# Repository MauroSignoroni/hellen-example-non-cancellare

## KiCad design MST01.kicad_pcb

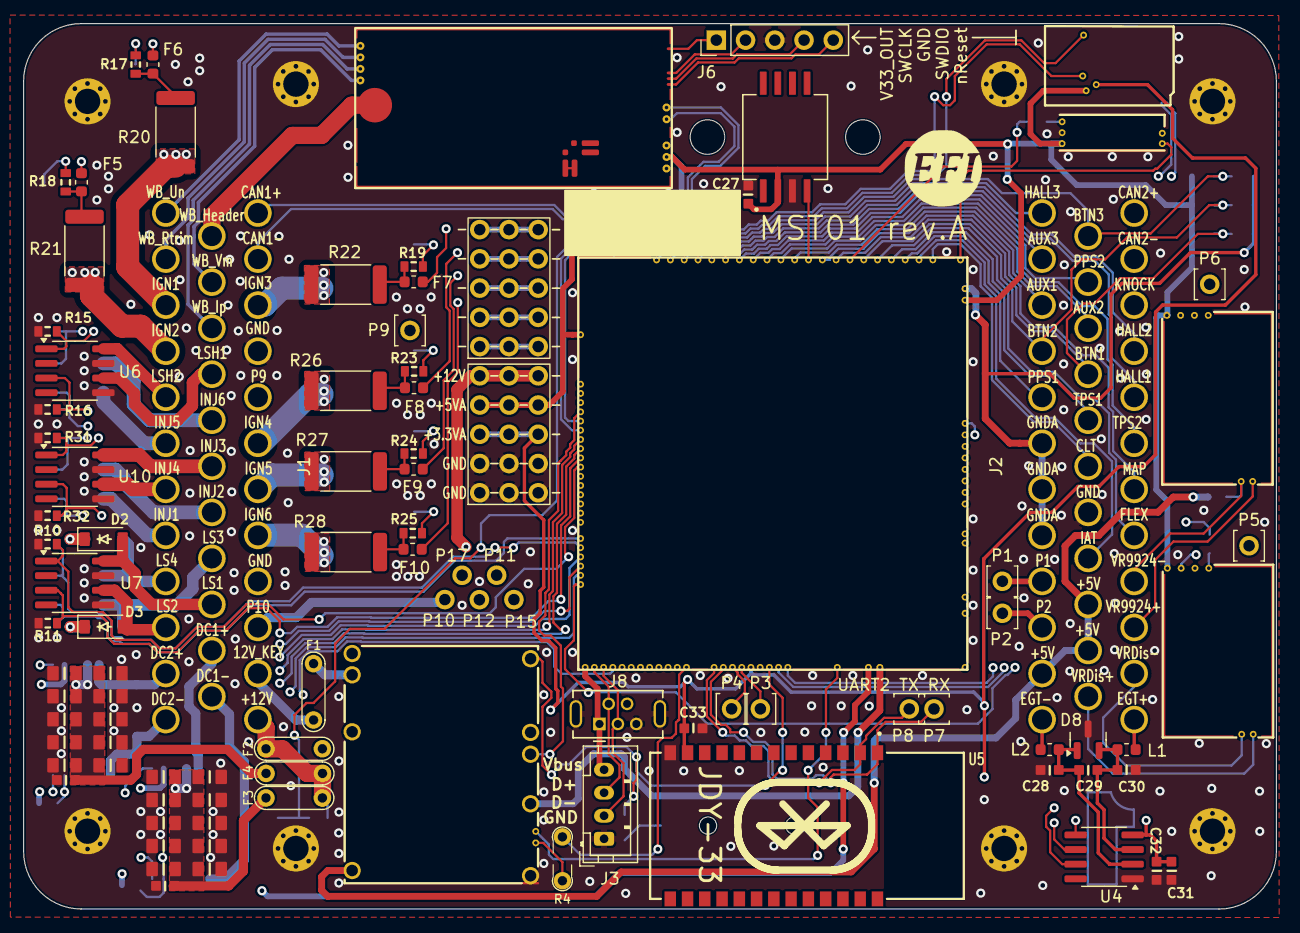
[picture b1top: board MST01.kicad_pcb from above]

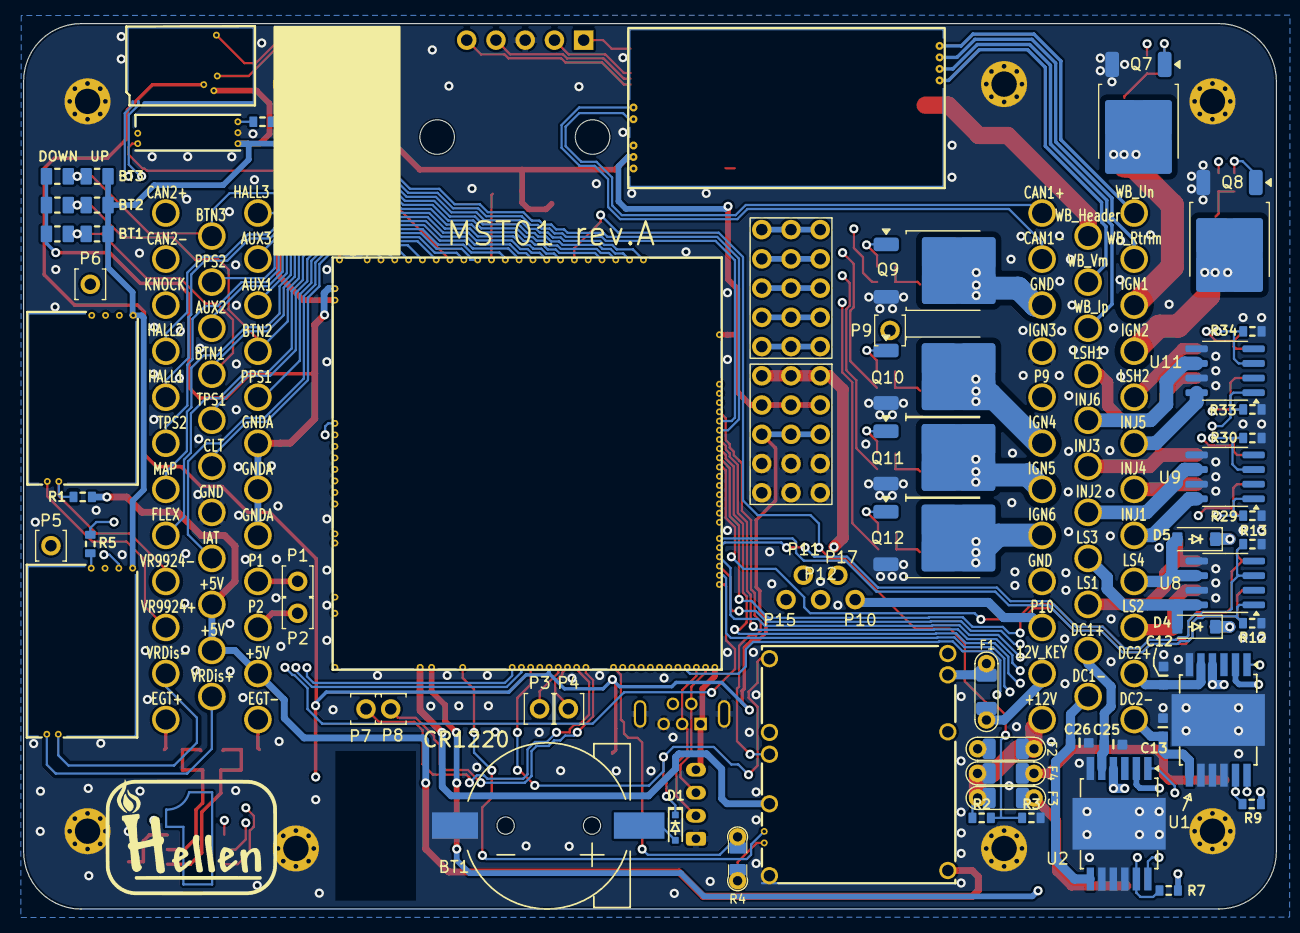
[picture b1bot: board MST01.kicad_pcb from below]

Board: 4 copper layers, 108.8 x 76.9 mm, 139 parts (45 on the bottom side), 147 nets.

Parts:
BT1: CR1220; CR1220-2
C1, C2, C3, C4, C5, C6, C7, C8, C9, C10, C14, C15, C16, C17, C18, C19, C20, C21, C22, C23: 10u; C0805
C11, C24, C27, C29, C31, C33: 100n; C0603
C12, C13, C25, C26, C28, C30: 10n; C0603
C32: 1u; C0603
D1: 1N4148WS; SOD-323
D2, D3, D4, D5: B5819W; SOD-123
D8: NUP2105L; SOT-23
F1, F2, F3, F4: 12H1500D; PAD-1206-PAD
F5, F6, F7, F8, F9, F10: 50mA; Fuse_0603_1608Metric
G1: RUSEFI_LOGO; rusefi_logo
G2: LOGO
G3, G4: PROTO_AREA
H1, H2: MountingHole; MountingHole_3mm
J1: AMPSeal-35-verticale-nero; ampseal-35-mia-con-pad-GND
J2: AMPSeal-35-verticale-bianco; ampseal-35-mia-con-pad-GND
J3: Conn_01x04_Pin; JST_PH_B4B-PH-K_1x04_P2.00mm_Vertical
J6: Conn_01x05_Pin; PinHeader_1x05_P2.54mm_Vertical
J8: USB_B_Mini; USB-MINI-B-VERTICAL
L1, L2: 470R@100MHz; L_0603_1608Metric
M1: Module-power_12and5V-0.3; power_12and5V
M2: Module-knock-0.2; knock
M3: Module-vr-discrete-0.5; vr-discrete
M4: Module-vr-max9924-0.1; vr-max9924
M5: Module-wbo-0.5; wbo
M6: Module:mega-mcu100/0.3; mega-mcu100
M7: Module-can-0.1; can
P1, P2, P3, P4, P5, P6, P7, P8, P9: Pad; PAD-TH
P10, P11, P12, P15, P17: Pad; PAD-TH-senza-serigrafia
Q7, Q8, Q9, Q10, Q11, Q12: ISL9V3040D3ST; TO-252-2
R1, R7, R9, R10, R11, R12, R13, R15, R16, R29, R30, R31, R32, R33, R34: 4.7k; R0603
R2: 33k; R0603
R3: 6.8k; R0603
R4: Jumper-Pad-Pad; PAD-0805-PAD
R5, R6: 0; R0603
R17, R18, R19, R23, R24, R25: 22; R0603
R20, R21, R22, R26, R27, R28: 0; R_2512_6332Metric
R35, R36, R37, R38, R39, R40: 10k; R0805
U1, U2: TLE9201SG; Infineon_PG-DSO-12-11
U4: MAX31855KASA; SOIC-8_3.9x4.9mm_P1.27mm
U5: JDY-33; JDY-33_mio
U6, U7, U8, U9, U10, U11: VNLD5160TR-E; SOIC-8_3.9x4.9mm_P1.27mm
U12: MPXH6400A; MPXH6400A-SSOP8

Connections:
+3.3V: M6.N21 (V33), R7.2, R9.2, U1.2 (VSO), U2.2 (VSO)
+3.3VA: C31.2, C32.2, C33.2, G3.3, G3.8, G3.13, M6.N15 (V33_SWITCHABLE), M7.V2 (CAN_VIO), U4.4 (V_{CC}), U5.12 (3V3)
+5V: M1.E4 (V5), M6.N22 (VCC)
+5VA: C27.2, G3.4, G3.9, G3.14, M2.E1 (V5A), M3.E4 (V5_IN), M4.E4 (V5_IN), M5.W1 (V5_IN), M6.E1 (V5A_SWITCHABLE), M6.W2 (V5A_SWITCHABLE), M7.V1 (V5), R38.2, R39.2, R40.2, U12.2 (Vs)
+5VP: J2.21, J2.22, J2.34, M1.V4 (5VP), R1.1
+12V: F2.1, F3.1, F4.1, J1.24, R2.2
+12V_RAW: D2.1 (K), D3.1 (K), D4.1 (K), D5.1 (K), F2.2, G3.5, G3.10, G3.15, M1.V1 (V12_PERM), M1.V3 (V12_RAW)
/2 DC Driver/PWR1: C1.2, C2.2, C3.2, C4.2, C5.2, C6.2, C7.2, C8.2, C9.2, C10.2, C11.2, F4.2, U1.4 (VS)
/2 DC Driver/PWR2: C14.2, C15.2, C16.2, C17.2, C18.2, C19.2, C20.2, C21.2, C22.2, C23.2, C24.2, F3.2, U2.4 (VS)
/12V_KEY: F1.1, J1.25
/ADC3: M6.S15 (IN_KNOCK_(PA2)), R5.2, R6.2
/AUX1: J2.26, M6.S11 (IN_O2S_/_CAN_WAKEUP_(PA0))
/AUX2: J2.15, M6.S10 (IN_O2S2_(PA1))
/AUX3: J2.25, M6.S7 (IN_AUX3_(PA7))
/BUTTON1: J2.16, M6.S14 (IN_CRANK_(PB1)), R35.2, R38.1
/BUTTON2: J2.27, M6.S16 (IN_CAM_(PA6)), R36.2, R39.1
/BUTTON3: J2.13, M6.S1 (IN_D4_(PE15)), R37.2, R40.1
/CAN1+: J1.35, M5.W4 (CANH), M6.W11 (CANH)
/CAN1-: J1.34, M5.W3 (CANL), M6.W12 (CANL)
/CAN2+: J2.1, M7.S2 (CANH)
/CAN2-: J2.2, M7.S1 (CANL)
/CLT: J2.18, M6.S21 (IN_CLT_(PC2))
/D+: J3.2, J8.3 (D+), M6.N3 (USBP_(PA12))
/D-: J3.3, J8.2 (D-), M6.N2 (USBM_(PA11))
/DC1_DIR: M6.E21 (OUT_PWM4_(PC8)), P15.1, U1.1 (DIR)
/DC1_DIS: M6.E8 (SPI2_MISO_(PB14)), R9.1, U1.11 (DIS)
/DC1_PWM: M6.E20 (OUT_PWM3_(PC7)), P17.1, U1.12 (PWM)
/DC2_DIR: M6.E9 (SPI2_MOSI_(PB15)), P12.1, U2.1 (DIR)
/DC2_DIS: M6.N4 (USBID_(PA10)), R7.1, U2.11 (DIS)
/DC2_PWM: M6.E22 (OUT_PWM5_(PC9)), P11.1, U2.12 (PWM)
/EGT/SPI_CS: M6.N9 (SPI3_CS_(PA15)), U4.6 (~CS)
/EGT/SPI_SCK: M6.N10 (SPI3_SCK_(PC10)), U4.5 (SCK)
/EGT/SPI_SO: M6.N11 (SPI3_MISO_(PC11)), U4.7 (SO)
/EGT/T+Filtrato: C29.2, C30.2, D8.2 (K), L1.2, U4.3 (T+)
/EGT/T-Filtrato: C28.2, C29.1, D8.1 (K), L2.2, U4.2 (T-)
/FLEX: J2.8, M6.S17 (IN_VSS_(PE11))
/HALL1: J2.5, M6.S4 (IN_D1_(PE12))
/HALL2: J2.4, M6.S3 (IN_D2_(PE13))
/HALL3: J2.24, M6.S2 (IN_D3_(PE14))
/IAT: J2.20, M6.S20 (IN_IAT_(PC3))
/IGN1: F6.2, M6.W10 (IGN1_(PC13))
/IGN2: F5.2, M6.W9 (IGN2_(PE5))
/IGN3: F7.2, M6.W8 (IGN3_(PE4))
/IGN4: F8.2, M6.W7 (IGN4_(PE3))
/IGN5: F9.2, M6.W6 (IGN5_(PE2))
/IGN6: F10.2, M6.W5 (IGN6_(PB8))
/IMP_VR_DISCRETE+: J2.23, M3.W2 (VR+)
/IMP_VR_DISCRETE-: J2.11, M3.W1 (VR-)
/IMP_VR_MAX9924+: J2.10, M4.W2 (VR+)
/IMP_VR_MAX9924-: J2.9, M4.W1 (VR-), R1.2
/INJ1: M6.E17 (OUT_INJ1_(PD3)), R29.2, U9.1 (IN1)
/INJ2: M6.E16 (OUT_INJ2_(PA9)), R30.2, U9.3 (IN2)
/INJ3: M6.E15 (OUT_INJ3_(PD11)), R31.2, U10.1 (IN1)
/INJ4: M6.E14 (OUT_INJ4_(PD10)), R32.2, U10.3 (IN2)
/INJ5: M6.E13 (OUT_INJ5_(PD2)), R33.2, U11.1 (IN1)
/INJ6: M6.E12 (OUT_INJ6_(PA8)), R34.2, U11.3 (IN2)
/INTERNAL_MAP: M6.S12 (IN_MAP2_(PC1)), U12.4 (Vout)
/IN_KNOCK: M2.E3 (OUT_KNOCK), R6.1
/IN_KNOCK_RAW: J2.3, M2.W1 (IN_KNOCK)
/IN_VIGN: F1.2, M1.V2 (IN_VIGN)
/LS1: M6.E11 (OUT_INJ7_(PD15)), R10.2, U7.1 (IN1)
/LS2: M6.E10 (OUT_INJ8_(PD12)), R11.2, U7.3 (IN2)
/LS3: M6.E18 (OUT_PWM1_(PD13)), R12.2, U8.1 (IN1)
/LS4: M6.E19 (OUT_PWM2_(PC6)), R13.2, U8.3 (IN2)
/LS_HOT1: M6.W4 (IGN7_(PB9)), R16.1, U6.3 (IN2)
/LS_HOT2: M6.W3 (IGN8_(PE6)), R15.1, U6.1 (IN1)
/MAP: J2.7, M6.S13 (IN_MAP1_(PC0))
/OUT_DC1+: C13.2, J1.1, U1.7 (OUT2)
/OUT_DC1-: C12.2, J1.2, U1.5 (OUT1)
/OUT_DC2+: C26.2, J1.13, U2.7 (OUT2)
/OUT_DC2-: C25.2, J1.14, U2.5 (OUT1)
/OUT_IGN1: J1.10, Q7.2 (C), R20.2
/OUT_IGN2: J1.9, Q8.2 (C), R21.2
/OUT_IGN3: J1.33, Q9.2 (C), R22.2
/OUT_IGN4: J1.30, Q10.2 (C), R26.2
/OUT_IGN5: J1.29, Q11.2 (C), R27.2
/OUT_IGN6: J1.28, Q12.2 (C), R28.2
/OUT_INJ1: J1.5, U9.8 (D1)
/OUT_INJ2: J1.17, U9.6 (D2)
/OUT_INJ3: J1.18, U10.8 (D1)
/OUT_INJ4: J1.6, U10.6 (D2)
/OUT_INJ5: J1.7, U11.8 (D1)
/OUT_INJ6: J1.19, U11.6 (D2)
/OUT_LS1: D2.2 (A), J1.15, U7.8 (D1)
/OUT_LS2: D3.2 (A), J1.3, U7.6 (D2)
/OUT_LS3: D4.2 (A), J1.16, U8.8 (D1)
/OUT_LS4: D5.2 (A), J1.4, U8.6 (D2)
/OUT_LS_HOT1: J1.20, U6.6 (D2)
/OUT_LS_HOT2: J1.8, U6.8 (D1)
/P1: J2.32, P1.1
/P2: J2.33, P2.1
/P9: J1.31, P9.1
/P10: J1.26, P10.1
/PG_5VP: M6.N12 (SPI3_MOSI_(PC12)), R4.2
/PPS1: J2.28, M6.S19 (IN_PPS_(PA3))
/PPS2: J2.14, M6.S8 (IN_AUX2_(PC4/PE9))
/PWR_EN: M1.E5 (EN_5VP), M6.N20 (OUT_PWR_EN_(PE10))
/SWCLK: J6.2, M5.W7 (SWCLK)
/SWDIO: J6.4, M5.W6 (SWDIO)
/TPS1: J2.17, M6.S18 (IN_TPS_(PA4))
/TPS2: J2.6, M6.S9 (IN_AUX1_(PB0))
/V33_OUT: J6.1, M5.W8 (V33_OUT)
/VBAT: D1.1 (K), M1.E1 (VBAT), M6.N17 (VBAT)
/VIGN: M1.E3 (VIGN), M6.E5 (IN_VIGN_(PA5))
/VMAIN: M6.S6 (IN_AUX4_(PC5)), R2.1, R3.2
/VREF1: M2.W2 (VREF), M6.S22 (VREF1)
/VR_DISCRETE: M3.E3 (OUT), M6.N18 (UART8_RX_(PE0)), P5.1
/VR_DISCRETE_A: M3.E2 (OUT_A), R5.1
/VR_DISCRETE_THR: M3.E1 (Thresh_IN), M6.E23 (OUT_PWM6_(PD14))
/VR_MAX9924: M4.E3 (OUT), M6.N19 (UART8_TX_(PE1)), P6.1
/Vbus: J3.4, J8.1 (VBUS), M6.N1 (VBUS)
/WBO_Heater: J1.23, M5.E5 (LSU_H+)
/WBO_Ip: J1.21, M5.E3 (LSU_Ip)
/WBO_Rtrim: J1.11, M5.E4 (LSU_Rtrim)
/WBO_Un: J1.12, M5.E1 (LSU_Un)
/WBO_Vm: J1.22, M5.E2 (LSU_Vm)
/nReset: J6.5, M5.W5 (nReset)
EGT+: J2.12, L1.1
EGT-: J2.35, L2.1
GND: BT1.2 (-), C1.1, C2.1, C3.1, C4.1, C5.1, C6.1, C7.1, C8.1, C9.1, C10.1, C11.1, C12.1, C13.1, C14.1, C15.1, C16.1, C17.1, C18.1, C19.1, C20.1, C21.1, C22.1, C23.1, C24.1, C25.1, C26.1, C27.1, C28.1, C30.1, C31.1, C32.1, C33.1, D8.3 (A), G3.1, G3.2, G3.6, G3.7, G3.11, G3.12, J1.27, J1.32, J1.36, J2.19, J2.36, J3.1, J6.3, J8.5 (GND), J8.6 (Shield), M1.S1 (GND), M2.E2 (GND), M3.G (GND), M4.G (GND), M5.E6 (LSU_H-), M5.G (GND), M6.G (GND), M7.E1 (GND), Q7.3 (E), Q8.3 (E), Q9.3 (E), Q10.3 (E), Q11.3 (E), Q12.3 (E), R3.1, R10.1, R11.1, R12.1, R13.1, R15.2, R16.2, R29.1, R30.1, R31.1, R32.1, R33.1, R34.1, U1.6 (GND), U1.8 (SI), U1.9 (CSN), U1.10 (SCK), U1.13 (GND), U2.6 (GND), U2.8 (SI), U2.9 (CSN), U2.10 (SCK), U2.13 (GND), U4.1 (GND), U5.13 (GND), U6.5 (S2), U6.7 (S1), U7.5 (S2), U7.7 (S1), U8.5 (S2), U8.7 (S1), U9.5 (S2), U9.7 (S1), U10.5 (S2), U10.7 (S1), U11.5 (S2), U11.7 (S1), U12.3 (GND)
GNDA: J2.29, J2.30, J2.31, M6.W1 (GNDA), R35.1, R36.1, R37.1
unnamed: BT1.1 (+), D1.2 (A)
unnamed: F5.1, R18.2, R21.1
unnamed: F6.1, R17.2, R20.1
unnamed: F7.1, R19.2, R22.1
unnamed: F8.1, R23.2, R26.1
unnamed: F9.1, R24.2, R27.1
unnamed: F10.1, R25.2, R28.1
unnamed: G4.1, G4.6, G4.11
unnamed: G4.5, G4.10, G4.15
unnamed: G4.2, G4.7, G4.12
unnamed: G4.3, G4.8, G4.13
unnamed: G4.4, G4.9, G4.14
unnamed: M1.E6 (PG_5VP), R4.1
unnamed: M5.J1 (SEL1), M5.J_GND1 (PULL_DOWN1)
unnamed: M6.N14a (LED_GREEN), P4.1
unnamed: M6.N14b (LED_YELLOW), P3.1
unnamed: M6.E6 (SPI2_CS_/_CAN2_RX_(PB12)), M7.V6 (CAN_RX)
unnamed: M6.E7 (SPI2_SCK_/_CAN2_TX_(PB13)), M7.V5 (CAN_TX)
unnamed: M6.N14 (UART2_RX_(PD6)), P7.1, U5.1 (TXD)
unnamed: M6.N13 (UART2_TX_(PD5)), P8.1, U5.2 (RXD)
unnamed: Q7.1 (G), R17.1
unnamed: Q8.1 (G), R18.1
unnamed: Q9.1 (G), R19.1
unnamed: Q10.1 (G), R23.1
unnamed: Q11.1 (G), R24.1
unnamed: Q12.1 (G), R25.1

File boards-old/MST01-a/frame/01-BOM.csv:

Comment,Designator,Footprint,LCSC Part #
"CR1220","BT1","CR1220-2","C70381"
"10u","C1","C0805","C15850"
"10u","C2","C0805","C15850"
"10u","C3","C0805","C15850"
"10u","C4","C0805","C15850"
"10u","C5","C0805","C15850"
"10u","C6","C0805","C15850"
"10u","C7","C0805","C15850"
"10u","C8","C0805","C15850"
"10u","C9","C0805","C15850"
"10u","C10","C0805","C15850"
"100n","C11","C0603","C14663"
"10n","C12","C0603","C57112"
"10n","C13","C0603","C57112"
"10u","C14","C0805","C15850"
"10u","C15","C0805","C15850"
"10u","C16","C0805","C15850"
"10u","C17","C0805","C15850"
"10u","C18","C0805","C15850"
"10u","C19","C0805","C15850"
"10u","C20","C0805","C15850"
"10u","C21","C0805","C15850"
"10u","C22","C0805","C15850"
"10u","C23","C0805","C15850"
"100n","C24","C0603","C14663"
"10n","C25","C0603","C57112"
"10n","C26","C0603","C57112"
"100n","C27","C0603","C14663"
"10n","C28","C0603","C57112"
"100n","C29","C0603","C14663"
"10n","C30","C0603","C57112"
"100n","C31","C0603","C14663"
"1u","C32","C0603","C15849"
"100n","C33","C0603","C14663"
"1N4148WS","D1","SOD-323","C2128"
"B5819W","D2","SOD-123","C8598"
"B5819W","D3","SOD-123","C8598"
"B5819W","D4","SOD-123","C8598"
"B5819W","D5","SOD-123","C8598"
"NUP2105L","D8","SOT-23","C284104"
"12H1500D","F1","PAD-1206-PAD","C182446"
"12H1500D","F2","PAD-1206-PAD","C182446"
"12H1500D","F3","PAD-1206-PAD","C182446"
"12H1500D","F4","PAD-1206-PAD","C182446"
"50mA","F5","Fuse_0603_1608Metric","C369141"
"50mA","F6","Fuse_0603_1608Metric","C369141"
"50mA","F7","Fuse_0603_1608Metric","C369141"
"50mA","F8","Fuse_0603_1608Metric","C369141"
"50mA","F9","Fuse_0603_1608Metric","C369141"
"50mA","F10","Fuse_0603_1608Metric","C369141"
"RUSEFI_LOGO","G1","rusefi_logo",""
"LOGO","G2","LOGO",""
"PROTO_AREA","G3","PROTO_AREA",""
"PROTO_AREA","G4","PROTO_AREA",""
"AMPSeal-35-verticale-nero","J1","ampseal-35-mia-con-pad-GND",""
"AMPSeal-35-verticale-bianco","J2","ampseal-35-mia-con-pad-GND",""
"Conn_01x04_Pin","J3","JST_PH_B4B-PH-K_1x04_P2.00mm_Vertical","C5305780"
"Conn_01x05_Pin","J6","PinHeader_1x05_P2.54mm_Vertical",""
"USB_B_Mini","J8","USB-MINI-B-VERTICAL","C13453"
"470R@100MHz","L1","L_0603_1608Metric","C97853"
"470R@100MHz","L2","L_0603_1608Metric","C97853"
"Module:power_12and5V/0.2","M1","power_12and5V",""
"Module:knock/0.2","M2","knock",""
"Module:vr-discrete/0.5","M3","vr-discrete",""
"Module:vr-max9924/0.1","M4","vr-max9924",""
"Module:wbo/0.5","M5","wbo",""
"Module:mega-mcu100/0.3","M6","mega-mcu100",""
"Module:can/0.1","M7","can",""
"Pad","P1","PAD-TH",""
"Pad","P2","PAD-TH",""
"Pad","P3","PAD-TH",""
"Pad","P4","PAD-TH",""
"Pad","P5","PAD-TH",""
"Pad","P6","PAD-TH",""
"Pad","P7","PAD-TH",""
"Pad","P8","PAD-TH",""
"Pad","P9","PAD-TH",""
"Pad","P10","PAD-TH-senza-serigrafia",""
"Pad","P15","PAD-TH-senza-serigrafia",""
"Pad","P16","PAD-TH-senza-serigrafia",""
"Pad","P17","PAD-TH-senza-serigrafia",""
"Pad","P18","PAD-TH-senza-serigrafia",""
"ISL9V3040D3ST","Q7","DPAK",""
"ISL9V3040D3ST","Q8","DPAK",""
"ISL9V3040D3ST","Q9","DPAK",""
"ISL9V3040D3ST","Q10","DPAK",""
"ISL9V3040D3ST","Q11","DPAK","C462128"
"ISL9V3040D3ST","Q12","DPAK","C462128"
"4.7k","R1","R0603",""
"33k","R2","R0603","C4216"
"6.8k","R3","R0603","C23212"
"Jumper-Pad-Pad","R4","PAD-0805-PAD","C17477"
"0","R5","R0603",""
"0","R6","R0603","C21189"
"4.7k","R9","R0603","C23162"
"4.7k","R10","R0603","C23162"
"4.7k","R11","R0603","C23162"
"4.7k","R12","R0603","C23162"
"4.7k","R13","R0603","C23162"
"4.7k","R14","R0603","C23162"
"4.7k","R15","R0603","C23162"
"4.7k","R16","R0603","C23162"
"22","R17","R0603","C23345"
"22","R18","R0603","C23345"
"22","R19","R0603","C23345"
"0","R20","R2512","C25469"
"0","R21","R2512","C25469"
"0","R22","R2512","C25469"
"22","R23","R0603","C23345"
"22","R24","R0603","C23345"
"22","R25","R0603","C23345"
"0","R26","R2512","C25469"
"0","R27","R2512",""
"0","R28","R2512",""
"4.7k","R29","R0603","C23162"
"4.7k","R30","R0603","C23162"
"4.7k","R31","R0603","C23162"
"4.7k","R32","R0603","C23162"
"4.7k","R33","R0603","C23162"
"4.7k","R34","R0603","C23162"
"10k","R35","R0805","C17414"
"10k","R36","R0805","C17414"
"10k","R37","R0805","C17414"
"10k","R38","R0805",""
"10k","R39","R0805",""
"10k","R40","R0805",""
"TLE9201SG","U1","Infineon_PG-DSO-12-11","C2653438"
"TLE9201SG","U2","Infineon_PG-DSO-12-11","C2653438"
"MAX31855KASA","U4","SO8","C52028"
"JDY-33","U5","JDY-33_mio","C9900001612"
"VNLD5160TR-E","U6","SO8","C377942"
"VNLD5160TR-E","U7","SO8","C377942"
"VNLD5160TR-E","U8","SO8","C377942"
"VNLD5160TR-E","U9","SO8","C377942"
"VNLD5160TR-E","U10","SO8","C377942"
"VNLD5160TR-E","U11","SO8","C377942"
"MPXH6400A","U12","MPXH6400A-SSOP8","C511770"

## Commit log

2025-02-06 Aggiunta Progetto PCB
2025-02-06 [skip actions] Auto-generated board v2.1
2025-02-06 Aggiornamento PCB
2025-02-06 Aggiornamento
2025-02-07 Aggiornamento Progetto
2025-02-12 Riprovo
2025-02-12 MST01-a1
2025-02-13 MST01-a2
2025-02-13 Rev. a3
2025-02-15 MST01-a5
